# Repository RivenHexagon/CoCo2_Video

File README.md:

# RHCCV - Color Computer 2 S-Video and Composite Mod with Audio 

The ***RHCCV*** is a video mod for the ***Tandy Radio Shack Color Computer 2***. The modification **replaces** the **original** video **module** (the shiny metal box) of the *CoCo2*. It features a **6-pin** or **4-pin** compatible **Mini DIN** connector with **S-Video**, **Composite Video** and **Audio** outputs.

The [/jlcpcb](https://github.com/RivenHexagon/CoCo2_Video/tree/main/jlcpcb) folder contains production-ready files that can be directly uploaded to [jlcpcb.com](https://jlcpcb.com/) for PCB manufacturing.

## Compatibility
The current printed circuit board layout is designed to fit the CoCo2 model with a **horizontally** mounted RF **modulator** case. However, the modification itself would **also** work on earlier CoCo2 versions that use a **vertically** mounted modulator box. The only **differences** are in the **pinout** and the PCB **form factor**. I intend to develop a **revised** PCB **layout** to **fit** the **earlier** form factor, with completion expected by January 2025.
## Assembly and Installation
### 4-pin Mini DIN installed *(S-Video only)*
The **PCB** populated with a **4-pin** Mini DIN connector delivers **S-Video** as the **only** available **output**. The **pinout** is **standard** S-Video, as described [here](https://en.wikipedia.org/wiki/S-Video "S-Video Wikipedia").

### 6-Pin Mini DIN installed *(S-Video, Composite and Audio)*
The **6-pin** connector installed on the **PCB** makes **all** outputs available **simultaneously**. However, this requires a **custom** made **breakout cable** in order to **access** the **signals** individually. A veteran **PS/2** cable can be **modified** but please note that in some cables **not all pins** are **connected**.

The 6-pin Mini DIN connector has the following **pinout**:
* Pin 1: **Audio** out
* Pin 2: **Composite** Video
* Pin 3: **GND**
* Pin 4: **GND**
* Pin 5: **Luma** (Y)
* Pin 6: **Chroma** (C)

The KiCad PCB design uses a custom footprint for *ASSMANN* Mini DIN Connectors:<br>
<https://www.assmann-wsw.com/uploads/datasheets/ASS_1622_CO.pdf>

### Installation
* Desolder the **clamps** of the **metal** box and the **pin headers** of the original video module from the **main board**. (It is recommended to use a **desoldering pump** and **solder wick**)
* Carefully **desolder** the ***MC1372*** from the PCB of the original video module.
* On the RHCCV **PCB**, install a 14-pin **[IC socket](https://www.assmann-wsw.com/uploads/datasheets/ASS_0810_CO.pdf)** for **U1**, rather than soldering the ***MC1372*** directly onto the board.
* Make sure that the **pins** of the *MC1372* are **free of solder** and plug it into the **IC socket** of the RHCCV. Mind the correct **orientation**.
* Populate the remaining components listed in the [Bill of Materials](https://github.com/RivenHexagon/CoCo2_Video/blob/main/TRS-80-VideoMod-BOM.pdf).

The new PCB uses the **same** pin headers as the **original** module and does not require any additional wires to be pulled.

## The Mod
The **design** draws **inspiration** from the research and work of ***[AC's 8-bit Zone](https://youtu.be/tayGsz7Xs3A "ACs 8-bit Zone - YouTube")*** on *YouTube*. The RHCCV mod **integrates** his **S-Video** and **Conmposite Video** circuits into a **single** PCB.

The use of **Mini DIN** connectors in this PCB design provides several **benefits**:
* **Preserves** the **original hardware** (except for desoldering the *MC1372*)
* **Eliminates loose cables** exiting the TRS-80 case
* **No case modification** for extra connectors required

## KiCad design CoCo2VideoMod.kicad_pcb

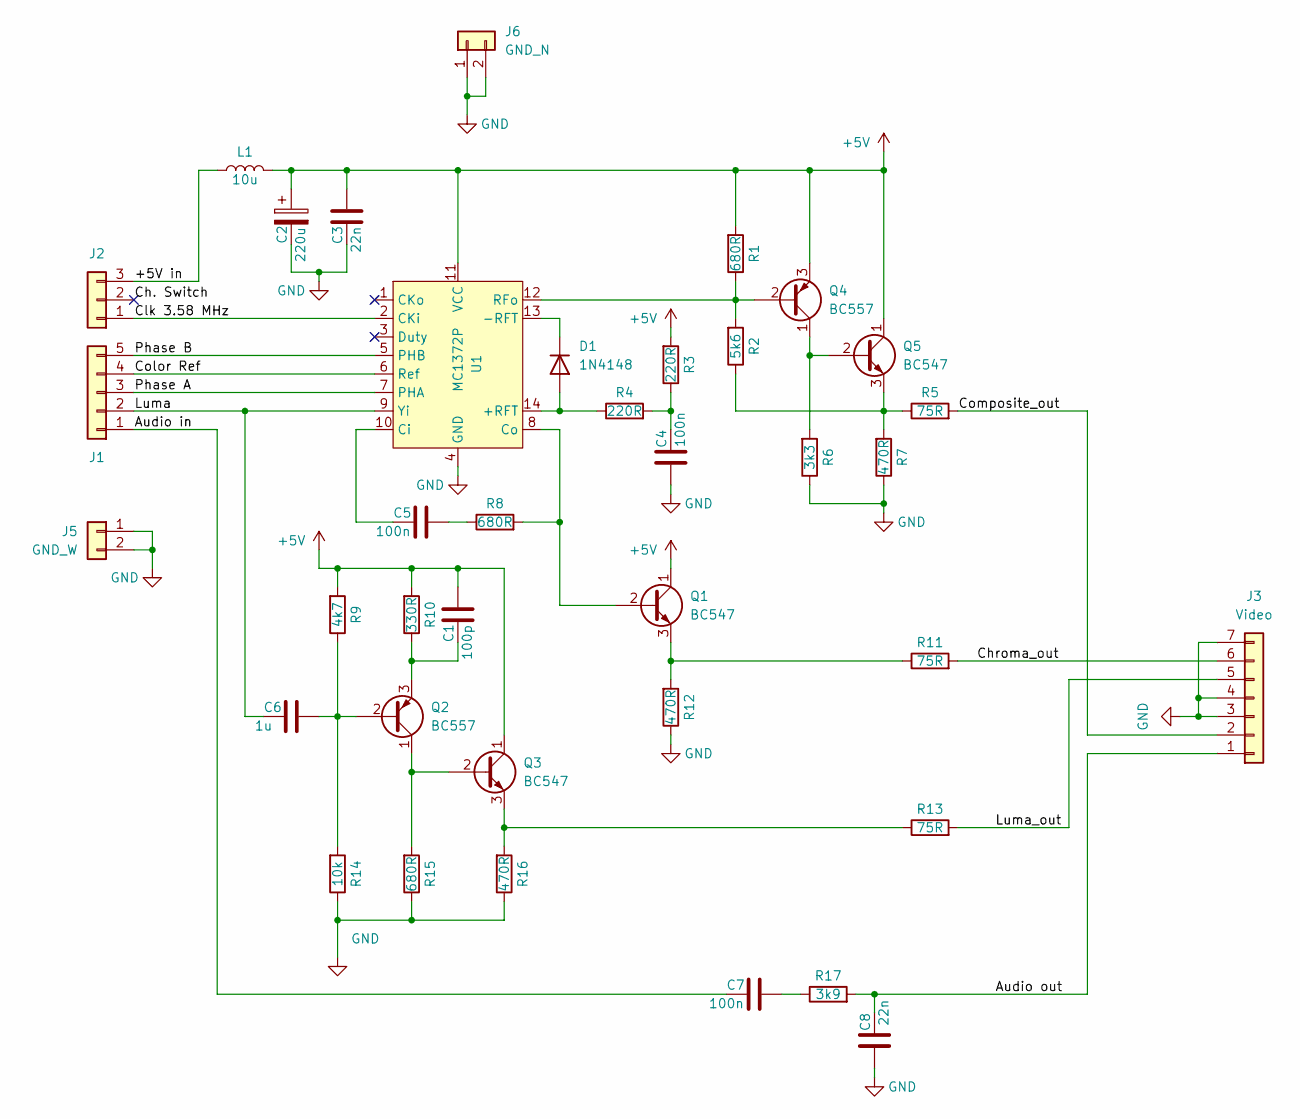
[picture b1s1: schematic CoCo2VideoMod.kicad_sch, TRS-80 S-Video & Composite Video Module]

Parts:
C1: 100p; C_Disc_D3.0mm_W2.0mm_P2.50mm
C2: 220u; CP_Radial_D6.3mm_P2.50mm
C3, C8: 22n; C_Rect_L7.0mm_W3.5mm_P5.00mm
C4, C5, C7: 100n; C_Rect_L9.0mm_W4.2mm_P7.50mm_MKT
C6: 1u; C_Rect_L7.0mm_W4.5mm_P5.00mm
D1: 1N4148; D_DO-35_SOD27_P2.54mm_Vertical_AnodeUp
J1: 20261043; PinHeader_1x05_P2.54mm_Vertical
J2: to PCB; PinHeader_1x03_P2.54mm_Vertical
J3: Video; Connector_Mini-DIN_Female_6Pin_2rows
J5: GND_W; PinHeader_1x02_P2.54mm_Vertical
J6: GND_N; PinHeader_1x02_P2.54mm_Vertical
L1: 10u; L_Axial_L6.6mm_D2.7mm_P10.16mm_Horizontal_Vishay_IM-2
Q1, Q3, Q5: BC547; TO-92_Inline
Q2, Q4: BC557; TO-92_Inline
R1, R15: 680R; R_Axial_DIN0207_L6.3mm_D2.5mm_P2.54mm_Vertical
R2: 5k6; R_Axial_DIN0207_L6.3mm_D2.5mm_P2.54mm_Vertical
R3, R4: 220R; R_Axial_DIN0207_L6.3mm_D2.5mm_P2.54mm_Vertical
R5, R11, R13: 75R; R_Axial_DIN0207_L6.3mm_D2.5mm_P2.54mm_Vertical
R6: 3k3; R_Axial_DIN0207_L6.3mm_D2.5mm_P2.54mm_Vertical
R7, R12, R16: 470R; R_Axial_DIN0207_L6.3mm_D2.5mm_P2.54mm_Vertical
R8: 680R; R_Axial_DIN0207_L6.3mm_D2.5mm_P7.62mm_Horizontal
R9: 4k7; R_Axial_DIN0207_L6.3mm_D2.5mm_P7.62mm_Horizontal
R10: 330R; R_Axial_DIN0207_L6.3mm_D2.5mm_P2.54mm_Vertical
R14: 10k; R_Axial_DIN0207_L6.3mm_D2.5mm_P2.54mm_Vertical
R17: 3k9; R_Axial_DIN0207_L6.3mm_D2.5mm_P2.54mm_Vertical
U1: MC1372P; DIP-14_W7.62mm

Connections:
+5V: C1.1, C2.1, C3.1, L1.2, Q1.1 (C), Q3.1 (C), Q4.3 (E), Q5.1 (C), R1.2, R3.2, R9.2, R10.2, U1.11 (VCC)
/+5V in: J2.3, L1.1
/Audio in: C7.2, J1.1
/Audio out: C8.2, J3.1, R17.2
/Ch. Switch: J2.2
/Chroma_out: J3.6, R11.2
/Clk 3.58 MHz: J2.1, U1.2 (CKi)
/Color Ref: J1.4, U1.6 (Ref)
/Composite_out: J3.2, R5.2
/Luma: C6.2, J1.2, U1.9 (Yi)
/Luma_out: J3.5, R13.2
/Phase A: J1.3, U1.7 (PHA)
/Phase B: J1.5, U1.5 (PHB)
GND: C2.2, C3.2, C4.1, C8.1, J3.3, J3.4, J3.7, J5.1, J5.2, J6.1, J6.2, R6.1, R7.1, R12.1, R14.1, R15.1, R16.1, U1.4 (GND)
unnamed: C4.2, R3.1, R4.2
unnamed: C5.1, R8.1
unnamed: C7.1, R17.1
unnamed: D1.2 (A), R4.1, U1.14 (+RFT)
unnamed: D1.1 (K), U1.13 (-RFT)
unnamed: Q1.2 (B), R8.2, U1.8 (Co)
unnamed: Q1.3 (E), R11.1, R12.2
unnamed: C6.1, Q2.2 (B), R9.1, R14.2
unnamed: Q2.1 (C), Q3.2 (B), R15.2
unnamed: C1.2, Q2.3 (E), R10.1
unnamed: Q3.3 (E), R13.1, R16.2
unnamed: Q4.2 (B), R1.1, R2.2, U1.12 (RFo)
unnamed: Q4.1 (C), Q5.2 (B), R6.2
unnamed: Q5.3 (E), R2.1, R5.1, R7.2
unnamed: C5.2, U1.10 (Ci)

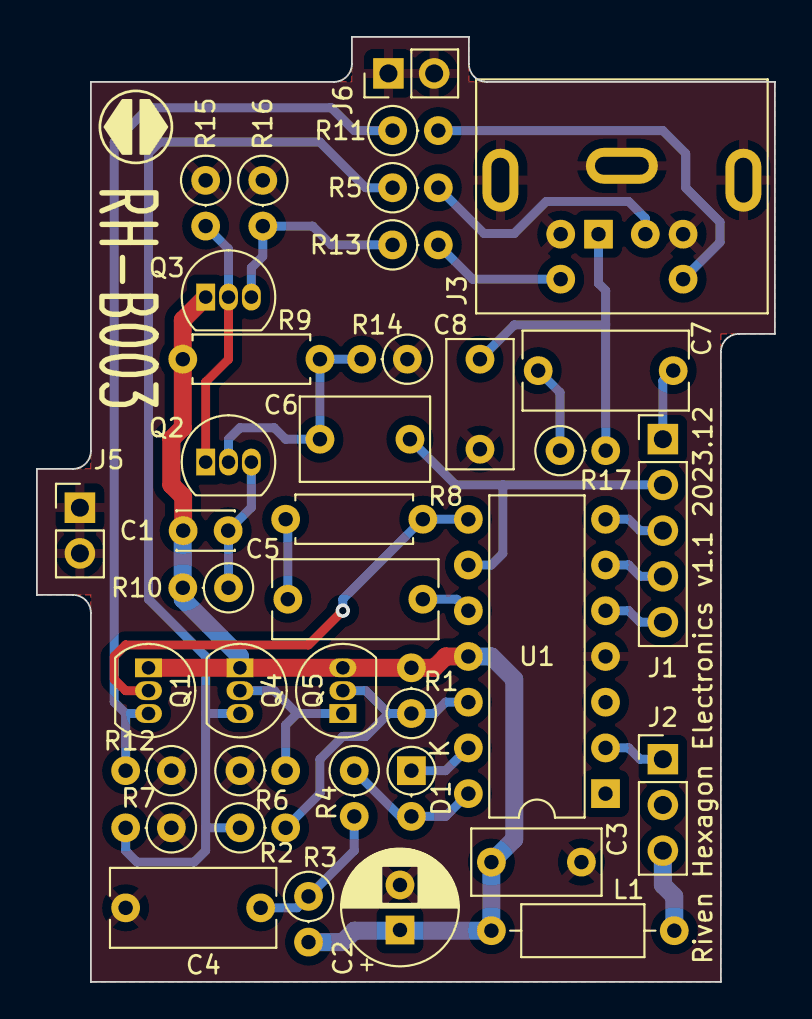
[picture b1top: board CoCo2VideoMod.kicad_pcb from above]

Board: 2 copper layers, 41.0 x 52.5 mm, 38 parts (0 on the bottom side), 28 nets.

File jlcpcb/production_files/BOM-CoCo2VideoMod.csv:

Comment,Designator,Footprint,LCSC
100n,C7,C_Rect_L9.0mm_W4.2mm_P7.50mm_MKT,
470R,R12,R_Axial_DIN0207_L6.3mm_D2.5mm_P2.54mm_Vertical,
100p,C1,C_Disc_D3.0mm_W2.0mm_P2.50mm,
220u,C2,CP_Radial_D6.3mm_P2.50mm,
MC1372P,U1,DIP-14_W7.62mm,
680R,R15,R_Axial_DIN0207_L6.3mm_D2.5mm_P2.54mm_Vertical,
3k9,R17,R_Axial_DIN0207_L6.3mm_D2.5mm_P2.54mm_Vertical,
10u,L1,L_Axial_L6.6mm_D2.7mm_P10.16mm_Horizontal_Vishay_IM-2,
3k3,R6,R_Axial_DIN0207_L6.3mm_D2.5mm_P2.54mm_Vertical,
BC557,Q4,TO-92_Inline,
470R,R7,R_Axial_DIN0207_L6.3mm_D2.5mm_P2.54mm_Vertical,
1N4148,D1,D_DO-35_SOD27_P2.54mm_Vertical_AnodeUp,
BC547,Q1,TO-92_Inline,
5k6,R2,R_Axial_DIN0207_L6.3mm_D2.5mm_P2.54mm_Vertical,
BC547,Q5,TO-92_Inline,
4k7,R9,R_Axial_DIN0207_L6.3mm_D2.5mm_P7.62mm_Horizontal,
330R,R10,R_Axial_DIN0207_L6.3mm_D2.5mm_P2.54mm_Vertical,
100n,C5,C_Rect_L9.0mm_W4.2mm_P7.50mm_MKT,
75R,R13,R_Axial_DIN0207_L6.3mm_D2.5mm_P2.54mm_Vertical,
22n,C8,C_Rect_L7.0mm_W3.5mm_P5.00mm,
100n,C4,C_Rect_L9.0mm_W4.2mm_P7.50mm_MKT,
10k,R14,R_Axial_DIN0207_L6.3mm_D2.5mm_P2.54mm_Vertical,
22n,C3,C_Rect_L7.0mm_W3.5mm_P5.00mm,
BC557,Q2,TO-92_Inline,
20261043,J1,PinHeader_1x05_P2.54mm_Vertical,
470R,R16,R_Axial_DIN0207_L6.3mm_D2.5mm_P2.54mm_Vertical,
1u,C6,C_Rect_L7.0mm_W4.5mm_P5.00mm,
Video,J3,Connector_Mini-DIN_Female_6Pin_2rows,
220R,R3,R_Axial_DIN0207_L6.3mm_D2.5mm_P2.54mm_Vertical,
to PCB,J2,PinHeader_1x03_P2.54mm_Vertical,
BC547,Q3,TO-92_Inline,
75R,R5,R_Axial_DIN0207_L6.3mm_D2.5mm_P2.54mm_Vertical,
680R,R1,R_Axial_DIN0207_L6.3mm_D2.5mm_P2.54mm_Vertical,
75R,R11,R_Axial_DIN0207_L6.3mm_D2.5mm_P2.54mm_Vertical,
220R,R4,R_Axial_DIN0207_L6.3mm_D2.5mm_P2.54mm_Vertical,
680R,R8,R_Axial_DIN0207_L6.3mm_D2.5mm_P7.62mm_Horizontal,

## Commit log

2023-09-18 circuit diagramm without s-video
2023-09-18 added local symbol library
2023-09-19 circuit diagramm completed
2023-09-19 footprint annotation
2023-09-19 mid routing
2023-09-19 croma and composite routing done
2023-09-19 midway chroma routing
2023-10-03 on luma layout
2023-10-03 Layout complete
2023-10-03 silk screen complete
2023-10-05 fab complete
2023-10-05 minor adjustments
2023-10-05 increased distance components to PCB edge
2023-12-01 production files JLC, production complete
2023-12-01 created BOM
2023-12-16 rotated connector, added GND pins
2023-12-16 deleted faulty production files
2023-12-16 adjusted GND pin position, added PCB description to silk screen, started README
2023-12-20 readme
2023-12-20 added JLCPCB production files
2024-11-06 Update README.md with compatibility note
2024-11-20 Update README.md on compatibility
